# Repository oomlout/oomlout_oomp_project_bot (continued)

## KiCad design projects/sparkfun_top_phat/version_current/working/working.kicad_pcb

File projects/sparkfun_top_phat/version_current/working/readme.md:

# Top_pHat by sparkfun  
This is a harvested standardized copy of a project from github.  
The original project can be found at:  
https://github.com/sparkfun/Top_pHat  
Please consult that link for additional, details, files, and license information.  
Note: It was auto harvested and if the original repo had more than one board file or anything out of the ordinary the files here are likely not representative.

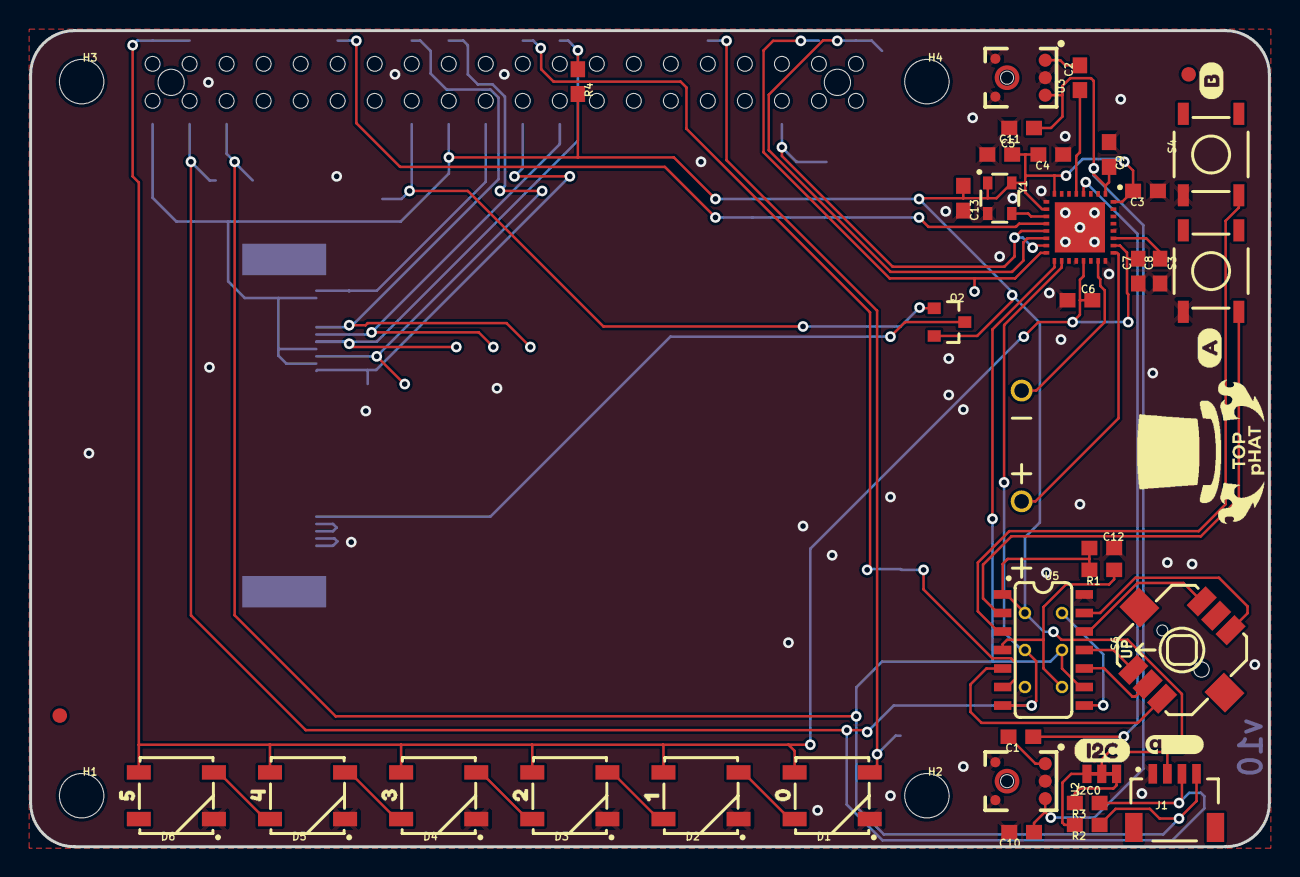
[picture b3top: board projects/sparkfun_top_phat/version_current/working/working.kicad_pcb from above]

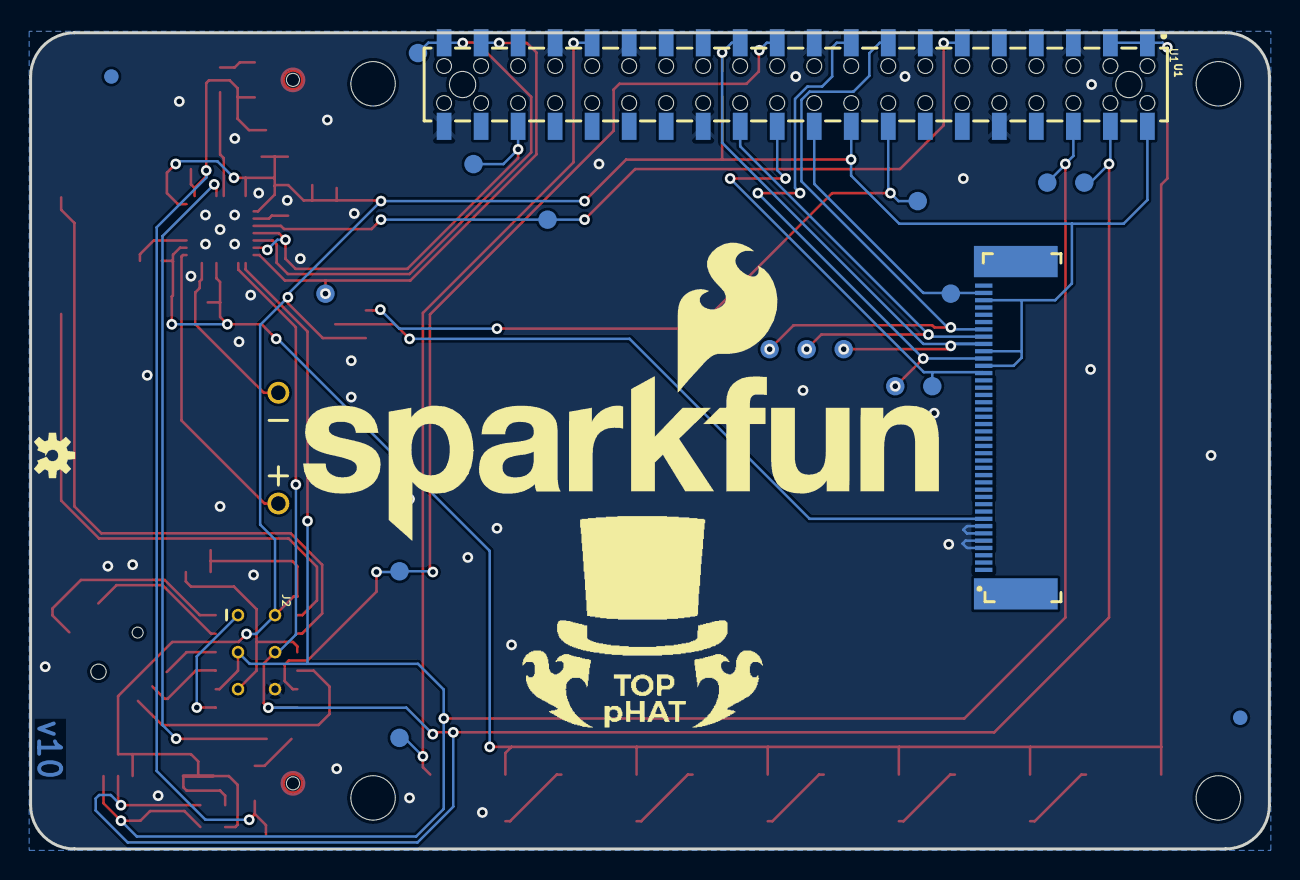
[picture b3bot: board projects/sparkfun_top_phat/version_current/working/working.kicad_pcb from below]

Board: 2 copper layers, 85.0 x 56.0 mm, 76 parts (23 on the bottom side), 44 nets.

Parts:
C1, C2: 2.2uF; 0603
C3, C4, C5, C10, C11, C12: 0.1uF; 0603
C6, C7, C8, C9: 4.7uF; 0603
C13: 10nF; 0603
D1, D2, D3, D4, D5, D6: WS2812B
FD1, FD2, FD3, FD4: FIDUCIAL1X2; FIDUCIAL-1X2
FRAME1: FRAME-LEDGER; CREATIVE_COMMONS
H1, H2, H3, H4: STAND-OFFTIGHT; STAND-OFF-TIGHT
I2C0: JUMPER-SMT_3_2-NC_TRACE_NO-SILK; SMT-JUMPER_3_2-NC_TRACE_NO-SILK
J1: QWIIC; JST04_1MM_RA
J2: AVR_SPI_PROG_3X2TESTPOINTS; 2X3_TEST_POINTS
J3: 2.4" TFT; FPC05040-17204
LOGO2: SFE_LOGO_NAME_FLAME.4_INCH; SFE_LOGO_NAME_FLAME_.4
LOGO3: QWIIC_LOGO_4MM; QWIIC_4MM
LOGO4: OSHW-LOGOS; OSHW-LOGO-S
LS2: CVS-1508; CVS-1508_PCBSPKR
Q2: 1.1A/60V/600mΩ; SOT23-3
R1, R4: 10k; 0603
R2, R3: 4.7k; 0603
S3, S4: MOMENTARY-SWITCH-SPST-SMD-5.2MM-TALL; TACTILE_SWITCH_SMD_5.2MM
S6: Joystick; JOYSTICK_MINI
TP1, TP2, TP3, TP4, TP5, TP6, TP7, TP8, TP9, TP10, TP11, TP12, TP13, TP14, TP15: TEST-POINT3X5; PAD.03X.05
U1: Raspberry Pi Header; RASPBERRY_PI_SHIELD_BOTTOM_ENTRY_NOHOLES
U2, U3: ADMP401
U4: WM8960; QFN-32
U5: ATTINY84; SO14
U$1, U$12: 2020#02#27#PNG
U$3: 00
U$4: 11
U$5: 22
U$6: A0
U$7: B1
U$8: I2C3
U$9: 33
U$10: 44
U$11: 55
Y1: 24 MHz; RESONATOR-SMD-3.2X2.5

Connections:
3.3V: C3.2, C4.2, C5.2, C12.1, C13.1, I2C0.2, J1.2, J2.2, J3.29, J3.31, J3.38, Q2.2, R1.2, R4.2, U1.1, U1.17, U4.8, U4.10, U4.32, U5.1, Y1.1, Y1.4
5V: C6.2, C7.2, D1.1, D2.1, D3.1, D4.1, D5.1, D6.1, U1.2, U1.4, U4.21, U4.26
ADC-DAT: TP10.P$1, U1.38, U4.16
BCLK: TP8.P$1, U1.12, U4.12
BTN_A: S3.3, U5.2
BTN_B: S4.3, U5.3
BTN_CENTER: S6.CTR, U5.10
BTN_DOWN: S6.D, U5.13
BTN_LEFT: S6.C, U5.5
BTN_RIGHT: S6.B, U5.12
BTN_UP: S6.A, U5.11
D/C: J3.30, TP14.P$1, U1.18
DAC-DAT: TP11.P$1, U1.40, U4.14
DAC-LRC: TP9.P$1, U1.35, U4.13, U4.15
GND: C3.1, C4.1, C5.1, C6.1, C7.1, C8.1, C9.1, C10.2, C11.2, C12.2, C13.2, D1.3, D2.3, D3.3, D4.3, D5.3, D6.3, J1.1, J2.6, J3.1, J3.4, J3.5, J3.6, J3.7, J3.11, J3.12, J3.13, J3.14, J3.15, J3.16, J3.17, J3.18, J3.19, J3.20, J3.21, J3.22, J3.23, J3.24, J3.25, J3.26, J3.27, J3.40, S3.1, S4.1, S6.GND, U1.6, U1.9, U1.14, U1.20, U1.25, U1.30, U1.34, U1.39, U2.2, U2.4, U2.6, U3.2, U3.4, U3.6, U4.9, U4.20, U4.24, U4.28, U4.PADDLE, U5.14, Y1.2
LED_DATA: D1.4, TP7.P$1, U1.32
LEFTMIC: C1.2, U2.1
MICBIAS: C9.2, C10.1, C11.1, U2.5, U3.5, U4.1
MISO: J2.1, U5.8
unnamed: D3.2, D4.4
unnamed: D4.2, D5.4
unnamed: D5.2, D6.4
unnamed: J3.8, Q2.3
unnamed: LS2.+, U4.25
unnamed: D1.2, D2.4
unnamed: D2.2, D3.4
unnamed: U4.11, Y1.3
unnamed: I2C0.3, R2.2
unnamed: I2C0.1, R3.2
unnamed: LS2.-, U4.23
unnamed: C1.1, U4.4
unnamed: C2.1, U4.5
unnamed: C8.2, U4.27
RIGHTMIC: C2.2, U3.1
SCK: J3.33, TP5.P$1, U1.23
SCL: J1.4, J2.3, R2.1, TP1.P$1, U1.5, U4.17, U5.9
SDA: J1.3, J2.4, R3.1, TP2.P$1, U1.3, U4.18, U5.7
SDI: J3.39, TP3.P$1, U1.19
SDO: J3.28, TP4.P$1, U1.21
~BKLITE: Q2.1, TP12.P$1, U1.15
~CS: J3.32, R4.1, TP6.P$1, U1.24
~INT: TP15.P$1, U1.22, U5.6
~RST_ATTINY: J2.5, R1.1, U5.4
~RST_SCREEN: J3.34, TP13.P$1, U1.16

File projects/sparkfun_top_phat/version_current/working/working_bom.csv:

"Id";"Designator";"Footprint";"Quantity";"Designation";"Supplier and ref";
1;"U$6";"A0";1;"";;;
2;"D2,D3,D6,D4,D5,D1";"WS2812B";6;"WS2812B";;;
3;"C3,C10,C5,C11,C12,C4";"0603";6;"0.1uF";;;
4;"FD3,FD1,FD2,FD4";"FIDUCIAL-1X2";4;"FIDUCIAL1X2";;;
5;"I2C0";"SMT-JUMPER_3_2-NC_TRACE_NO-SILK";1;"JUMPER-SMT_3_2-NC_TRACE_NO-SILK";;;
6;"U$4";"11";1;"";;;
7;"U$10";"44";1;"";;;
8;"U5";"SO14";1;"ATTINY84";;;
9;"U$9";"33";1;"";;;
10;"R1,R4";"0603";2;"10k";;;
11;"Y1";"RESONATOR-SMD-3.2X2.5";1;"24 MHz";;;
12;"R3,R2";"0603";2;"4.7k";;;
13;"LOGO3";"QWIIC_4MM";1;"QWIIC_LOGO_4MM";;;
14;"C2,C1";"0603";2;"2.2uF";;;
15;"U2,U3";"ADMP401";2;"ADMP401";;;
16;"H4,H1,H2,H3";"STAND-OFF-TIGHT";4;"STAND-OFFTIGHT";;;
17;"C8,C9,C6,C7";"0603";4;"4.7uF";;;
18;"C13";"0603";1;"10nF";;;
19;"U$3";"00";1;"";;;
20;"U$5";"22";1;"";;;
21;"J1";"JST04_1MM_RA";1;"QWIIC";;;
22;"U4";"QFN-32";1;"WM8960";;;
23;"U$11";"55";1;"";;;
24;"U$1,U$12";"2020#02#27#PNG";2;"";;;
25;"S3,S4";"TACTILE_SWITCH_SMD_5.2MM";2;"MOMENTARY-SWITCH-SPST-SMD-5.2MM-TALL";;;
26;"U$7";"B1";1;"";;;
27;"U$8";"I2C3";1;"";;;
28;"S6";"JOYSTICK_MINI";1;"Joystick";;;
29;"LS2";"CVS-1508_PCBSPKR";1;"CVS-1508";;;
30;"Q2";"SOT23-3";1;"1.1A/60V/600mΩ";;;
31;"FRAME1";"CREATIVE_COMMONS";1;"FRAME-LEDGER";;;
32;"TP6,TP2,TP8,TP14,TP5,TP11,TP9,TP4,TP7,TP15,TP12,TP13,TP3,TP10,TP1";"PAD.03X.05";15;"TEST-POINT3X5";;;
33;"U1";"RASPBERRY_PI_SHIELD_BOTTOM_ENTRY_NOHOLES";1;"Raspberry Pi Header";;;
34;"LOGO4";"OSHW-LOGO-S";1;"OSHW-LOGOS";;;
35;"LOGO2";"SFE_LOGO_NAME_FLAME_.4";1;"SFE_LOGO_NAME_FLAME.4_INCH";;;
36;"J3";"FPC05040-17204";1;"2.4" TFT";;;
37;"J2";"2X3_TEST_POINTS";1;"AVR_SPI_PROG_3X2TESTPOINTS";;;

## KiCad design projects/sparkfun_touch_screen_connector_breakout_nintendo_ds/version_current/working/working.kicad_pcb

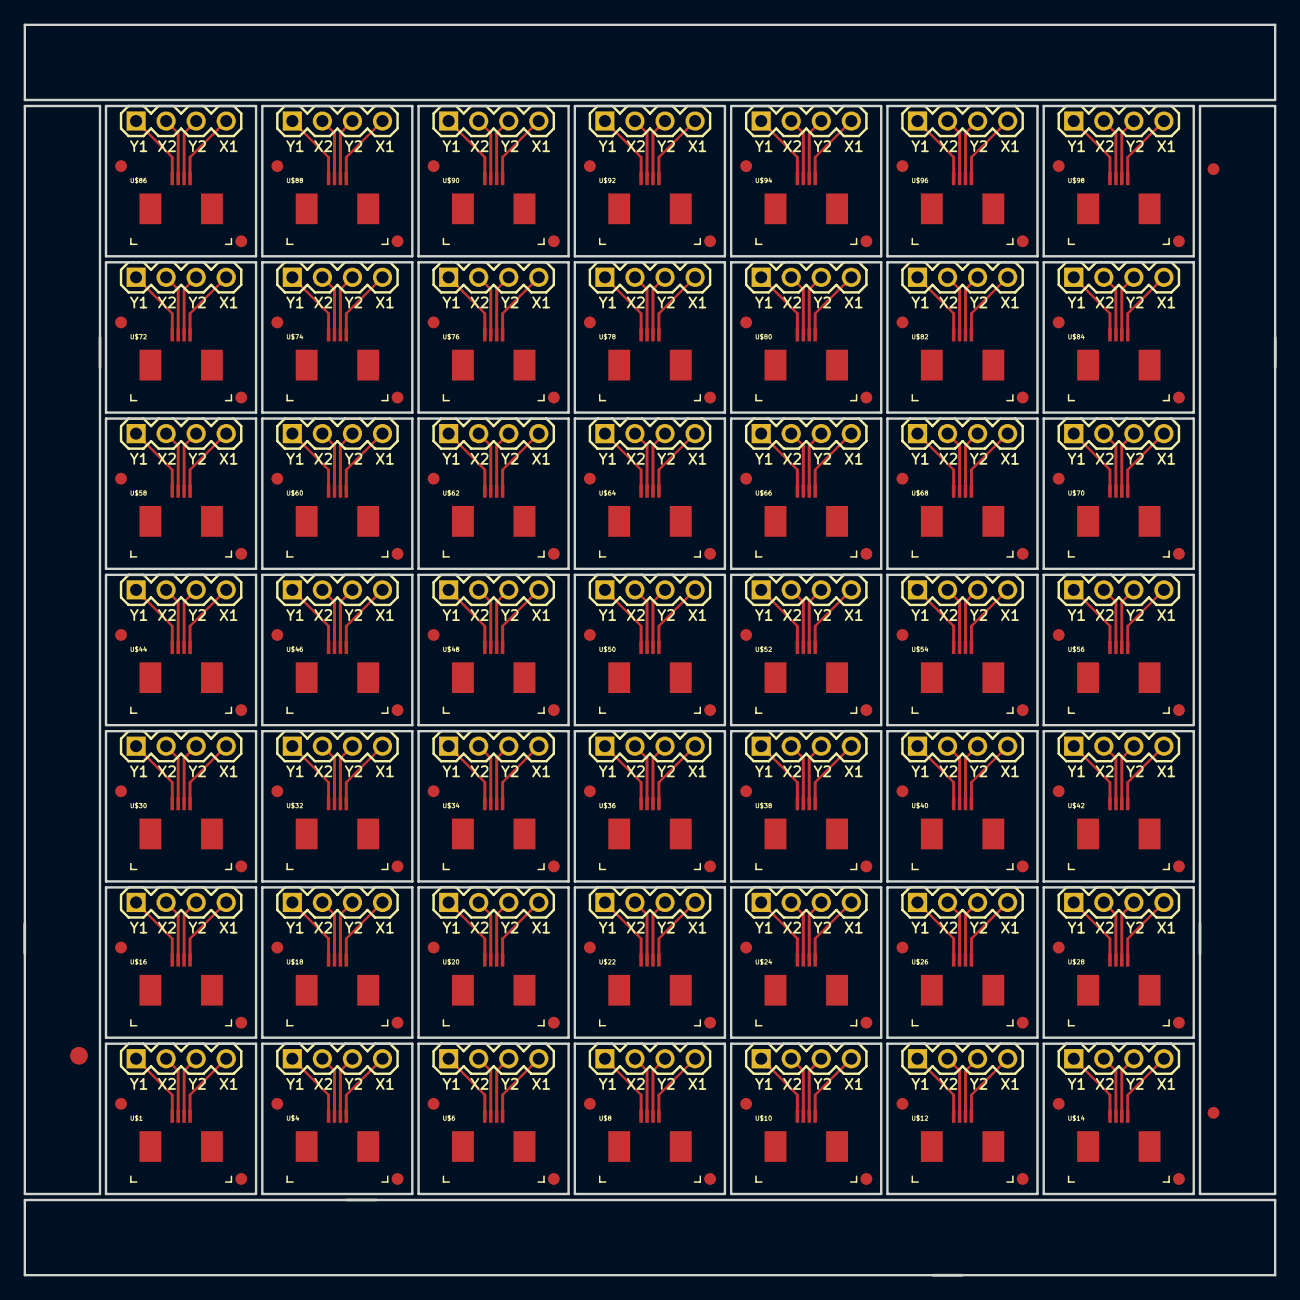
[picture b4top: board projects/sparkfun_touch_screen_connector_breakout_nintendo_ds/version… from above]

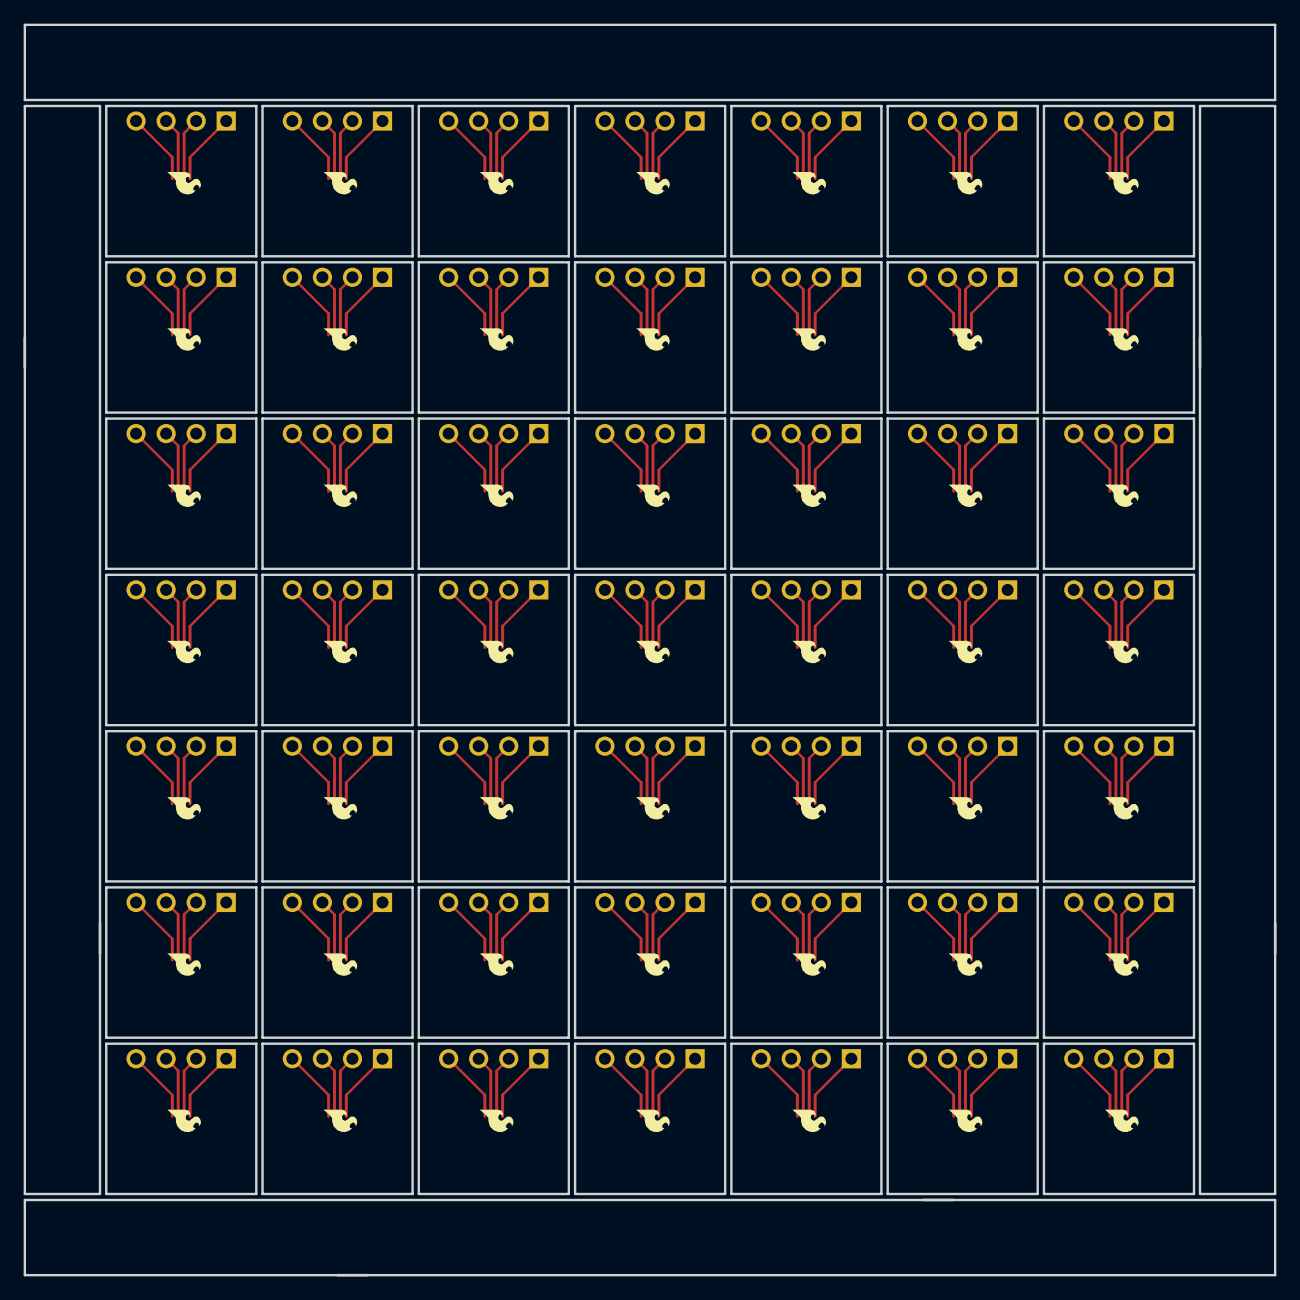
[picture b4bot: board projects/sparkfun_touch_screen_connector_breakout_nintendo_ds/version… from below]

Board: 16 copper layers, 105.7 x 105.7 mm, 248 parts (49 on the bottom side), 196 nets.

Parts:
E$1: FIDUCIAL-1.5X3
E$5, E$6: FIDUCIAL-1X2
FID1, FID2, FID3, FID4, FID5, FID6, FID7, FID8, FID9, FID10, FID11, FID12, FID13, FID14, FID15, FID16, FID17, FID18, FID19, FID20, FID21, FID22, FID23, FID24, FID25, FID26, FID27, FID28, FID29, FID30, FID31, FID32, FID33, FID34, FID35, FID36, FID37, FID38, FID39, FID40, FID41, FID42, FID43, FID44, FID45, FID46, FID47, FID48, FID49, FID50, FID51, FID52, FID53, FID54, FID55, FID56, FID57, FID58, FID59, FID60, FID61, FID62, FID63, FID64, FID65, FID66, FID67, FID68, FID69, FID70, FID71, FID72, FID73, FID74, FID75, FID76, FID77, FID78, FID79, FID80, FID81, FID82, FID83, FID84, FID85, FID86, FID87, FID88, FID89, FID90, FID91, FID92, FID93, FID94, FID95, FID96, FID97, FID98: FIDUCIAL1X2; FIDUCIAL-1X2
JP1, JP2, JP3, JP4, JP5, JP6, JP7, JP8, JP9, JP10, JP11, JP12, JP13, JP14, JP15, JP16, JP17, JP18, JP19, JP20, JP21, JP22, JP23, JP24, JP25, JP26, JP27, JP28, JP29, JP30, JP31, JP32, JP33, JP34, JP35, JP36, JP37, JP38, JP39, JP40, JP41, JP42, JP43, JP44, JP45, JP46, JP47, JP48, JP49: 1X04
U$1, U$4, U$6, U$8, U$10, U$12, U$14, U$16, U$18, U$20, U$22, U$24, U$26, U$28, U$30, U$32, U$34, U$36, U$38, U$40, U$42, U$44, U$46, U$48, U$50, U$52, U$54, U$56, U$58, U$60, U$62, U$64, U$66, U$68, U$70, U$72, U$74, U$76, U$78, U$80, U$82, U$84, U$86, U$88, U$90, U$92, U$94, U$96, U$98: DS_TOUCH_CONNECTOR
U$2, U$3, U$5, U$7, U$9, U$11, U$13, U$15, U$17, U$19, U$21, U$23, U$25, U$27, U$29, U$31, U$33, U$35, U$37, U$39, U$41, U$43, U$45, U$47, U$49, U$51, U$53, U$55, U$57, U$59, U$61, U$63, U$65, U$67, U$69, U$71, U$73, U$75, U$77, U$79, U$81, U$83, U$85, U$87, U$89, U$91, U$93, U$95, U$97: LOGO-SFESK; SFE-LOGO-FLAME

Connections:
unnamed: JP1.4, U$1.X1
unnamed: JP1.3, U$1.Y2
unnamed: JP1.2, U$1.X2
unnamed: JP1.1, U$1.Y1
unnamed: JP2.4, U$4.X1
unnamed: JP2.3, U$4.Y2
unnamed: JP2.2, U$4.X2
unnamed: JP2.1, U$4.Y1
unnamed: JP3.4, U$6.X1
unnamed: JP3.3, U$6.Y2
unnamed: JP3.2, U$6.X2
unnamed: JP3.1, U$6.Y1
unnamed: JP4.4, U$8.X1
unnamed: JP4.3, U$8.Y2
unnamed: JP4.2, U$8.X2
unnamed: JP4.1, U$8.Y1
unnamed: JP5.4, U$10.X1
unnamed: JP5.3, U$10.Y2
unnamed: JP5.2, U$10.X2
unnamed: JP5.1, U$10.Y1
unnamed: JP6.4, U$12.X1
unnamed: JP6.3, U$12.Y2
unnamed: JP6.2, U$12.X2
unnamed: JP6.1, U$12.Y1
unnamed: JP7.4, U$14.X1
unnamed: JP7.3, U$14.Y2
unnamed: JP7.2, U$14.X2
unnamed: JP7.1, U$14.Y1
unnamed: JP8.4, U$16.X1
unnamed: JP8.3, U$16.Y2
unnamed: JP8.2, U$16.X2
unnamed: JP8.1, U$16.Y1
unnamed: JP9.4, U$18.X1
unnamed: JP9.3, U$18.Y2
unnamed: JP9.2, U$18.X2
unnamed: JP9.1, U$18.Y1
unnamed: JP10.4, U$20.X1
unnamed: JP10.3, U$20.Y2
unnamed: JP10.2, U$20.X2
unnamed: JP10.1, U$20.Y1
unnamed: JP11.4, U$22.X1
unnamed: JP11.3, U$22.Y2
unnamed: JP11.2, U$22.X2
unnamed: JP11.1, U$22.Y1
unnamed: JP12.4, U$24.X1
unnamed: JP12.3, U$24.Y2
unnamed: JP12.2, U$24.X2
unnamed: JP12.1, U$24.Y1
unnamed: JP13.4, U$26.X1
unnamed: JP13.3, U$26.Y2
unnamed: JP13.2, U$26.X2
unnamed: JP13.1, U$26.Y1
unnamed: JP14.4, U$28.X1
unnamed: JP14.3, U$28.Y2
unnamed: JP14.2, U$28.X2
unnamed: JP14.1, U$28.Y1
unnamed: JP15.4, U$30.X1
unnamed: JP15.3, U$30.Y2
unnamed: JP15.2, U$30.X2
unnamed: JP15.1, U$30.Y1
unnamed: JP16.4, U$32.X1
unnamed: JP16.3, U$32.Y2
unnamed: JP16.2, U$32.X2
unnamed: JP16.1, U$32.Y1
unnamed: JP17.4, U$34.X1
unnamed: JP17.3, U$34.Y2
unnamed: JP17.2, U$34.X2
unnamed: JP17.1, U$34.Y1
unnamed: JP18.4, U$36.X1
unnamed: JP18.3, U$36.Y2
unnamed: JP18.2, U$36.X2
unnamed: JP18.1, U$36.Y1
unnamed: JP19.4, U$38.X1
unnamed: JP19.3, U$38.Y2
unnamed: JP19.2, U$38.X2
unnamed: JP19.1, U$38.Y1
unnamed: JP20.4, U$40.X1
unnamed: JP20.3, U$40.Y2
unnamed: JP20.2, U$40.X2
unnamed: JP20.1, U$40.Y1
unnamed: JP21.4, U$42.X1
unnamed: JP21.3, U$42.Y2
unnamed: JP21.2, U$42.X2
unnamed: JP21.1, U$42.Y1
unnamed: JP22.4, U$44.X1
unnamed: JP22.3, U$44.Y2
unnamed: JP22.2, U$44.X2
unnamed: JP22.1, U$44.Y1
unnamed: JP23.4, U$46.X1
unnamed: JP23.3, U$46.Y2
unnamed: JP23.2, U$46.X2
unnamed: JP23.1, U$46.Y1
unnamed: JP24.4, U$48.X1
unnamed: JP24.3, U$48.Y2
unnamed: JP24.2, U$48.X2
unnamed: JP24.1, U$48.Y1
unnamed: JP25.4, U$50.X1
unnamed: JP25.3, U$50.Y2
unnamed: JP25.2, U$50.X2
unnamed: JP25.1, U$50.Y1
unnamed: JP26.4, U$52.X1
unnamed: JP26.3, U$52.Y2
unnamed: JP26.2, U$52.X2
unnamed: JP26.1, U$52.Y1
unnamed: JP27.4, U$54.X1
unnamed: JP27.3, U$54.Y2
unnamed: JP27.2, U$54.X2
unnamed: JP27.1, U$54.Y1
unnamed: JP28.4, U$56.X1
unnamed: JP28.3, U$56.Y2
unnamed: JP28.2, U$56.X2
unnamed: JP28.1, U$56.Y1
unnamed: JP29.4, U$58.X1
unnamed: JP29.3, U$58.Y2
unnamed: JP29.2, U$58.X2
unnamed: JP29.1, U$58.Y1
unnamed: JP30.4, U$60.X1
unnamed: JP30.3, U$60.Y2
unnamed: JP30.2, U$60.X2
unnamed: JP30.1, U$60.Y1
unnamed: JP31.4, U$62.X1
unnamed: JP31.3, U$62.Y2
unnamed: JP31.2, U$62.X2
unnamed: JP31.1, U$62.Y1
unnamed: JP32.4, U$64.X1
unnamed: JP32.3, U$64.Y2
unnamed: JP32.2, U$64.X2
unnamed: JP32.1, U$64.Y1
unnamed: JP33.4, U$66.X1
unnamed: JP33.3, U$66.Y2
unnamed: JP33.2, U$66.X2
unnamed: JP33.1, U$66.Y1
unnamed: JP34.4, U$68.X1
unnamed: JP34.3, U$68.Y2
unnamed: JP34.2, U$68.X2
unnamed: JP34.1, U$68.Y1
unnamed: JP35.4, U$70.X1
unnamed: JP35.3, U$70.Y2
unnamed: JP35.2, U$70.X2
unnamed: JP35.1, U$70.Y1
unnamed: JP36.4, U$72.X1
unnamed: JP36.3, U$72.Y2
unnamed: JP36.2, U$72.X2
unnamed: JP36.1, U$72.Y1
unnamed: JP37.4, U$74.X1
unnamed: JP37.3, U$74.Y2
unnamed: JP37.2, U$74.X2
unnamed: JP37.1, U$74.Y1
unnamed: JP38.4, U$76.X1
unnamed: JP38.3, U$76.Y2
unnamed: JP38.2, U$76.X2
unnamed: JP38.1, U$76.Y1
unnamed: JP39.4, U$78.X1
unnamed: JP39.3, U$78.Y2
unnamed: JP39.2, U$78.X2
unnamed: JP39.1, U$78.Y1
unnamed: JP40.4, U$80.X1
unnamed: JP40.3, U$80.Y2
unnamed: JP40.2, U$80.X2
unnamed: JP40.1, U$80.Y1
unnamed: JP41.4, U$82.X1
unnamed: JP41.3, U$82.Y2
unnamed: JP41.2, U$82.X2
unnamed: JP41.1, U$82.Y1
unnamed: JP42.4, U$84.X1
unnamed: JP42.3, U$84.Y2
unnamed: JP42.2, U$84.X2
unnamed: JP42.1, U$84.Y1
unnamed: JP43.4, U$86.X1
unnamed: JP43.3, U$86.Y2
unnamed: JP43.2, U$86.X2
unnamed: JP43.1, U$86.Y1
unnamed: JP44.4, U$88.X1
unnamed: JP44.3, U$88.Y2
unnamed: JP44.2, U$88.X2
unnamed: JP44.1, U$88.Y1
unnamed: JP45.4, U$90.X1
unnamed: JP45.3, U$90.Y2
unnamed: JP45.2, U$90.X2
unnamed: JP45.1, U$90.Y1
unnamed: JP46.4, U$92.X1
unnamed: JP46.3, U$92.Y2
unnamed: JP46.2, U$92.X2
unnamed: JP46.1, U$92.Y1
unnamed: JP47.4, U$94.X1
unnamed: JP47.3, U$94.Y2
unnamed: JP47.2, U$94.X2
unnamed: JP47.1, U$94.Y1
unnamed: JP48.4, U$96.X1
unnamed: JP48.3, U$96.Y2
unnamed: JP48.2, U$96.X2
unnamed: JP48.1, U$96.Y1
unnamed: JP49.4, U$98.X1
unnamed: JP49.3, U$98.Y2
unnamed: JP49.2, U$98.X2
unnamed: JP49.1, U$98.Y1

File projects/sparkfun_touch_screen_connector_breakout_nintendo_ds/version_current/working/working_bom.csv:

"Id";"Designator";"Footprint";"Quantity";"Designation";"Supplier and ref";
1;"U$10,U$62,U$60,U$64,U$14,U$78,U$34,U$86,U$72,U$32,U$74,U$16,U$76,U$70,U$38,U$6,U$4,U$26,U$90,U$94,U$44,U$40,U$88,U$24,U$48,U$82,U$20,U$28,U$80,U$42,U$68,U$54,U$56,U$84,U$22,U$1,U$46,U$52,U$92,U$58,U$96,U$36,U$12,U$98,U$8,U$50,U$66,U$30,U$18";"DS_TOUCH_CONNECTOR";49;"DS_TOUCH_CONNECTOR";;;
2;"FID72,FID11,FID44,FID38,FID70,FID96,FID33,FID17,FID20,FID23,FID48,FID86,FID19,FID49,FID15,FID8,FID90,FID34,FID52,FID27,FID61,FID79,FID62,FID84,FID83,FID64,FID26,FID73,FID69,FID98,FID46,FID12,FID45,FID94,FID60,FID78,FID59,FID89,FID5,FID51,FID35,FID2,FID81,FID76,FID6,FID43,FID16,FID56,FID31,FID95,FID66,FID88,FID10,FID58,FID53,FID71,FID87,FID14,FID41,FID85,FID91,FID13,FID77,FID22,FID7,FID18,FID28,FID9,FID40,FID4,FID80,FID63,FID67,FID24,FID42,FID65,FID82,FID30,FID54,FID57,FID39,FID1,FID32,FID93,FID21,FID97,FID47,FID55,FID37,FID50,FID3,FID74,FID25,FID29,FID75,FID92,FID68,FID36";"FIDUCIAL-1X2";98;"FIDUCIAL1X2";;;
3;"JP6,JP2,JP9,JP41,JP34,JP42,JP22,JP26,JP31,JP16,JP19,JP30,JP38,JP49,JP13,JP46,JP27,JP12,JP11,JP43,JP35,JP40,JP39,JP23,JP20,JP33,JP32,JP1,JP7,JP3,JP8,JP4,JP5,JP28,JP24,JP29,JP25,JP21,JP37,JP48,JP17,JP45,JP18,JP36,JP10,JP44,JP47,JP15,JP14";"1X04";49;"";;;
4;"E$1";"FIDUCIAL-1.5X3";1;"";;;
5;"E$6,E$5";"FIDUCIAL-1X2";2;"";;;
6;"U$63,U$77,U$41,U$79,U$9,U$91,U$69,U$29,U$37,U$43,U$83,U$89,U$93,U$31,U$27,U$3,U$21,U$87,U$5,U$7,U$47,U$45,U$73,U$13,U$2,U$11,U$49,U$35,U$97,U$61,U$75,U$23,U$33,U$57,U$71,U$65,U$25,U$39,U$15,U$53,U$55,U$59,U$95,U$51,U$17,U$85,U$19,U$81,U$67";"SFE-LOGO-FLAME";49;"LOGO-SFESK";;;

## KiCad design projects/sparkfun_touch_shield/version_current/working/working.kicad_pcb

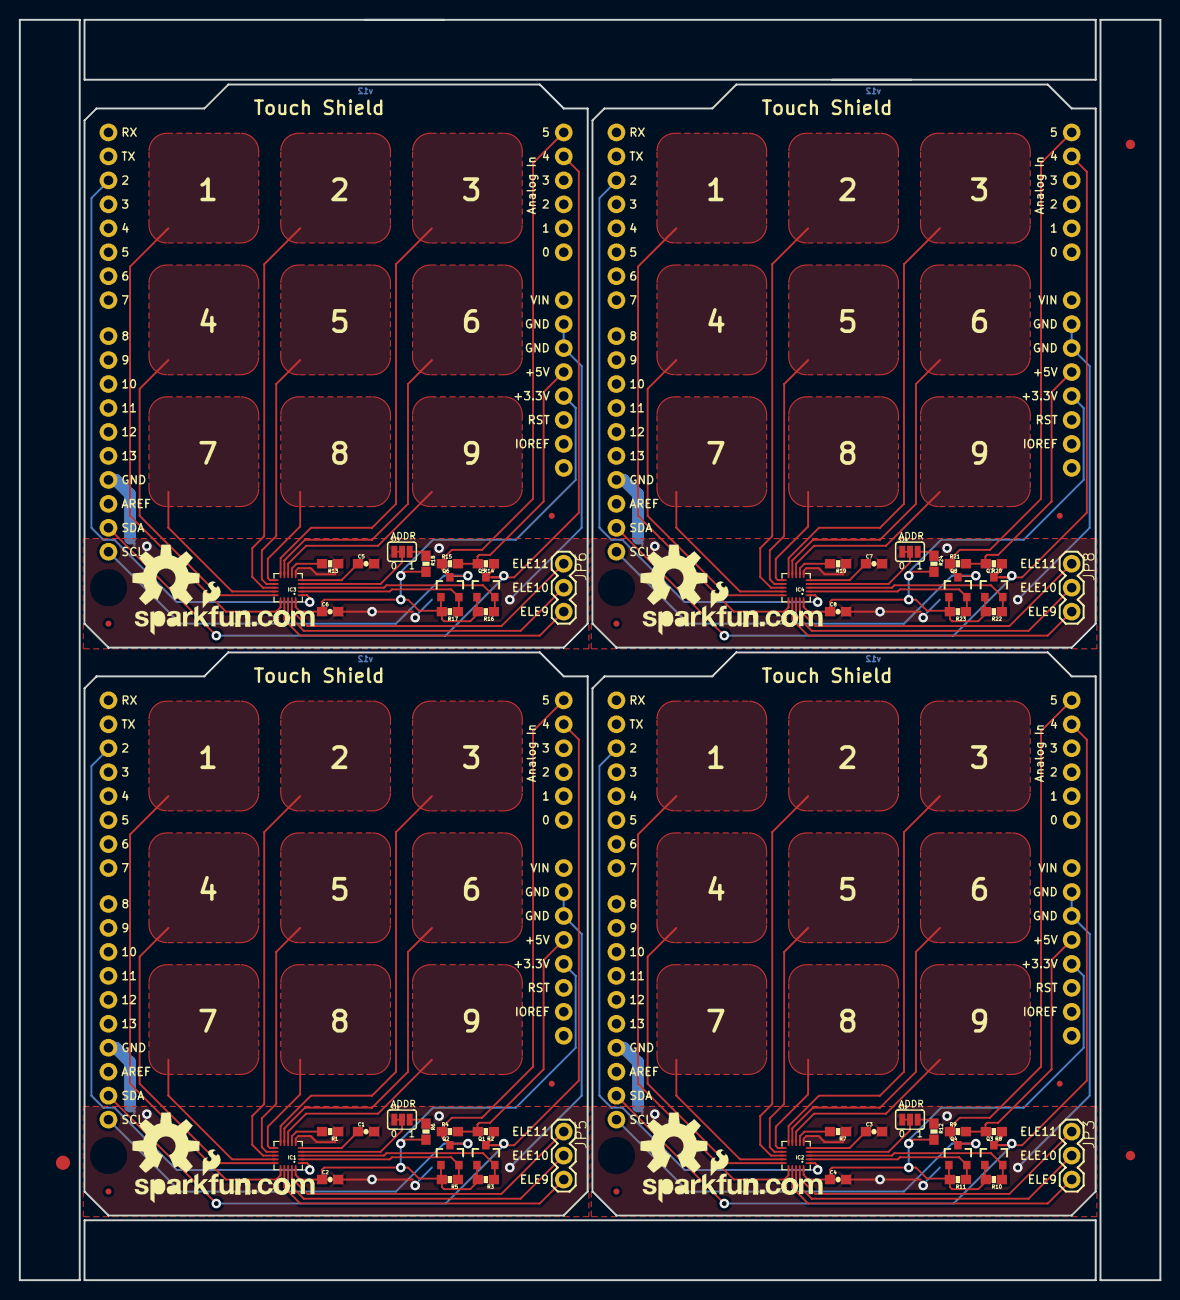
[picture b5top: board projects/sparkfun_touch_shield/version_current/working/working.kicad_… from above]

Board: 2 copper layers, 120.9 x 133.6 mm, 75 parts (0 on the bottom side), 60 nets.

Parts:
C1, C2, C3, C4, C5, C6, C7, C8: 0.1uF; 0603-CAP
E$1: FIDUCIAL-1.5X3
E$4, E$8: FIDUCIAL-1X2
FID1, FID2, FID3, FID4, FID5, FID6, FID7, FID8: FIDUCIALUFIDUCIAL; MICRO-FIDUCIAL
IC1, IC2, IC3, IC4: MPR121; QFN-20-0.4MM-V2
JP1, JP2, JP4, JP7: LOGO-SFENEW; SFE-NEW-WEBLOGO
JP3, JP5, JP6, JP8: extra; 1X03
Q1, Q2, Q3, Q4, Q5, Q6, Q7, Q8: BSS138; SOT23-3
R1, R7, R13, R19: 75k; 0603-RES
R2, R3, R4, R5, R8, R9, R10, R11, R14, R15, R16, R17, R20, R21, R22, R23: 10k; 0603-RES
R6, R12, R18, R24: 10K; 0603-RES
SJ1, SJ2, SJ3, SJ4: SJ_3_PASTE1&2
U1, U2, U3, U4: ARDUINO_R3_SHIELD; UNO_R3_SHIELD
U$1, U$2, U$3, U$5: OSHW-LOGOL; OSHW-LOGO-L

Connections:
3.3V: C2.1, IC1.20, Q1.1, Q2.1, R3.2, R5.2, R6.2, U1.3.3V
3.3V1: C4.1, IC2.20, Q3.1, Q4.1, R10.2, R11.2, R12.2, U2.3.3V
3.3V2: C6.1, IC3.20, Q5.1, Q6.1, R16.2, R17.2, R18.2, U3.3.3V
3.3V3: C8.1, IC4.20, Q7.1, Q8.1, R22.2, R23.2, R24.2, U4.3.3V
5V: R2.2, R4.2, U1.5V
5V1: R8.2, R9.2, U2.5V
5V2: R14.2, R15.2, U3.5V
5V3: R20.2, R21.2, U4.5V
*IRQ: IC1.1, U1.D2
*IRQ1: IC2.1, U2.D2
*IRQ2: IC3.1, U3.D2
*IRQ3: IC4.1, U4.D2
ELE1: IC2.19, JP3.1
ELE2: IC2.18, JP3.2
ELE3: IC2.17, JP3.3
ELE4: IC3.19, JP6.1
ELE5: IC3.18, JP6.2
ELE6: IC3.17, JP6.3
ELE7: IC4.19, JP8.1
ELE8: IC4.18, JP8.2
ELE9: IC1.17, JP5.3
ELE10: IC1.18, JP5.2
ELE11: IC1.19, JP5.1
ELE12: IC4.17, JP8.3
GND: C1.2, C2.2, IC1.6, R1.1, SJ1.1, U1.GND@0, U1.GND@1, U1.GND@2
GND1: C3.2, C4.2, IC2.6, R7.1, SJ2.1, U2.GND@0, U2.GND@1, U2.GND@2
GND2: C5.2, C6.2, IC3.6, R13.1, SJ3.1, U3.GND@0, U3.GND@1, U3.GND@2
GND3: C7.2, C8.2, IC4.6, R19.1, SJ4.1, U4.GND@0, U4.GND@1, U4.GND@2
unnamed: IC1.4, SJ1.2
unnamed: R6.1, SJ1.3
unnamed: IC2.4, SJ2.2
unnamed: R12.1, SJ2.3
unnamed: IC3.4, SJ3.2
unnamed: R18.1, SJ3.3
unnamed: IC4.4, SJ4.2
unnamed: R24.1, SJ4.3
REXT: IC1.7, R1.2
REXT1: IC2.7, R7.2
REXT2: IC3.7, R13.2
REXT3: IC4.7, R19.2
SCL_H: Q2.3, R4.1, U1.A5, U1.SCL
SCL_H1: Q4.3, R9.1, U2.A5, U2.SCL
SCL_H2: Q6.3, R15.1, U3.A5, U3.SCL
SCL_H3: Q8.3, R21.1, U4.A5, U4.SCL
SCL_L: IC1.2, Q2.2, R5.1
SCL_L1: IC2.2, Q4.2, R11.1
SCL_L2: IC3.2, Q6.2, R17.1
SCL_L3: IC4.2, Q8.2, R23.1
SDA_H: Q1.3, R2.1, U1.A4, U1.SDA
SDA_H1: Q3.3, R8.1, U2.A4, U2.SDA
SDA_H2: Q5.3, R14.1, U3.A4, U3.SDA
SDA_H3: Q7.3, R20.1, U4.A4, U4.SDA
SDA_L: IC1.3, Q1.2, R3.1
SDA_L1: IC2.3, Q3.2, R10.1
SDA_L2: IC3.3, Q5.2, R16.1
SDA_L3: IC4.3, Q7.2, R22.1
VREG: C1.1, IC1.5
VREG1: C3.1, IC2.5
VREG2: C5.1, IC3.5
VREG3: C7.1, IC4.5

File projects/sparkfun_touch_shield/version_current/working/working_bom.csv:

"Id";"Designator";"Footprint";"Quantity";"Designation";"Supplier and ref";
1;"Q1,Q6,Q3,Q5,Q7,Q2,Q4,Q8";"SOT23-3";8;"BSS138";;;
2;"U$2,U$1,U$3,U$5";"OSHW-LOGO-L";4;"OSHW-LOGOL";;;
3;"R3,R11,R14,R23,R17,R10,R22,R16,R2,R8,R9,R15,R21,R4,R20,R5";"0603-RES";16;"10k";;;
4;"JP2,JP1,JP4,JP7";"SFE-NEW-WEBLOGO";4;"LOGO-SFENEW";;;
5;"FID4,FID2,FID3,FID1,FID8,FID7,FID5,FID6";"MICRO-FIDUCIAL";8;"FIDUCIALUFIDUCIAL";;;
6;"R24,R6,R18,R12";"0603-RES";4;"10K";;;
7;"U2,U4,U3,U1";"UNO_R3_SHIELD";4;"ARDUINO_R3_SHIELD";;;
8;"SJ3,SJ1,SJ2,SJ4";"SJ_3_PASTE1&2";4;"";;;
9;"IC1,IC4,IC3,IC2";"QFN-20-0.4MM-V2";4;"MPR121";;;
10;"R1,R13,R7,R19";"0603-RES";4;"75k";;;
11;"C1,C3,C4,C8,C7,C2,C6,C5";"0603-CAP";8;"0.1uF";;;
12;"JP8,JP5,JP6,JP3";"1X03";4;"extra";;;
13;"E$4,E$8";"FIDUCIAL-1X2";2;"";;;
14;"E$1";"FIDUCIAL-1.5X3";1;"";;;

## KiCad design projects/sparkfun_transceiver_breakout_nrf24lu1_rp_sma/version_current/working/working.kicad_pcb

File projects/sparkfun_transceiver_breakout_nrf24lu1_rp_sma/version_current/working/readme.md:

# Transceiver_Breakout-nRF24LU1_RP-SMA by sparkfun  
This is a harvested standardized copy of a project from github.  
The original project can be found at:  
https://github.com/sparkfun/Transceiver_Breakout-nRF24LU1_RP-SMA  
Please consult that link for additional, details, files, and license information.  
Note: It was auto harvested and if the original repo had more than one board file or anything out of the ordinary the files here are likely not representative.

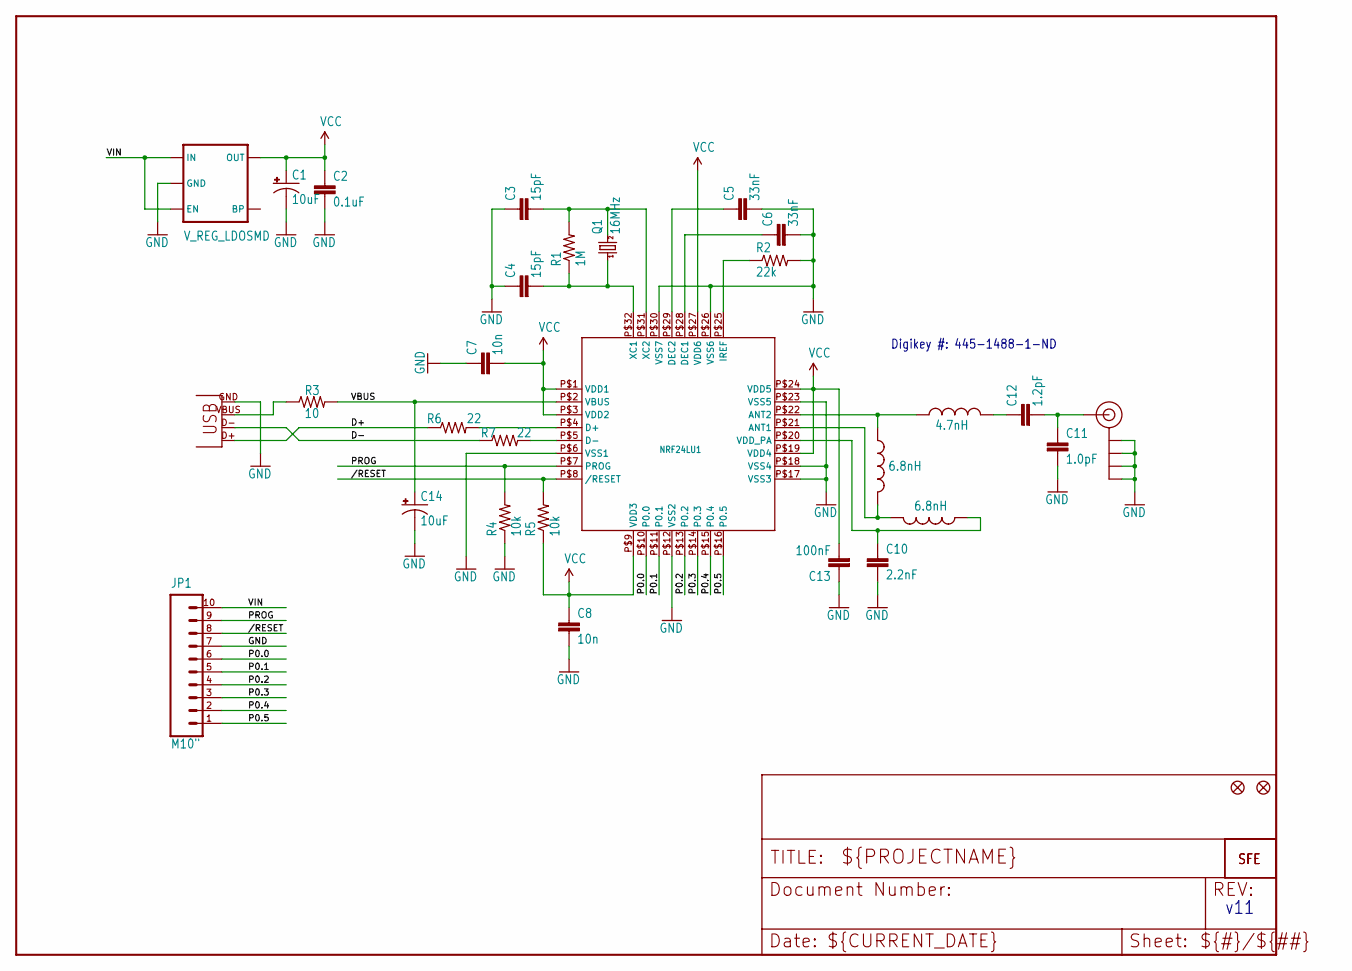
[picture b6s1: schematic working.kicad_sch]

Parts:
C1, C14: 10uF; EIA3216
C2: 0.1uF; 0402-CAP
C3, C4: 15pF; 0402-CAP
C5, C6: 33nF; 0402-CAP
C7, C8: 10n; 0402-CAP
C10: 2.2nF; 0402-CAP
C11: 1.0pF; 0402-CAP
C12: 1.2pF; 0402-CAP
C13: 100nF; 0402-CAP
J$1: SMA_EDGE; SMA-EDGE
JP1: M10"; 1X10
JP2: LOGO-SFENEW; SFE-NEW-WEBLOGO
L1: 4.7nH; C0402
L2, L3: 6.8nH; C0402
Q1: 16MHz; CRYSTAL-SMD-5X3
R1: 1M; 0402-RES
R2: 22k; 0402-RES
R3: 10; 1206
R4, R5: 10k; 0402-RES
R6, R7: 22; 0402-RES
U1: V_REG_LDOSMD; SOT23-5
U2: NRF24LU1; QFN-32
U$12, U$13: FIDUCIAL1X2; FIDUCIAL-1X2
U$14: LOGO-SFESK; SFE-LOGO-FLAME
X1: USBSMD; USB-MINIB

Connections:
/RESET: JP1.8, R5.2, U2.P$8 (/RESET)
D+: R6.1, X1.D+
D-: R7.1, X1.D-
GND: C1.C (-), C2.2, C3.1, C4.1, C5.2, C6.2, C7.1, C8.2, C10.2, C11.2, C13.1, C14.C (-), J$1.GND@0, J$1.GND@1, J$1.GND@2, J$1.GND@3, JP1.7, R2.2, R4.1, U1.2 (GND), U2.P$6 (VSS1), U2.P$12 (VSS2), U2.P$17 (VSS3), U2.P$18 (VSS4), U2.P$23 (VSS5), U2.P$26 (VSS6), U2.P$30 (VSS7), X1.GND
unnamed: C3.2, Q1.3 (2), R1.2, U2.P$31 (XC2)
unnamed: C4.2, Q1.1, R1.1, U2.P$32 (XC1)
unnamed: L1.1, L2.1, U2.P$22 (ANT2)
unnamed: C5.1, U2.P$29 (DEC2)
unnamed: R6.2, U2.P$4 (D+)
unnamed: R3.1, X1.VBUS
unnamed: R7.2, U2.P$5 (D-)
unnamed: C6.1, U2.P$28 (DEC1)
unnamed: R2.1, U2.P$25 (IREF)
unnamed: C12.1, L1.2
unnamed: C11.1, C12.2, J$1.SIG (SIGNAL)
unnamed: L2.2, L3.2, U2.P$21 (ANT1)
unnamed: C10.1, L3.1, U2.P$20 (VDD_PA)
P0.0: JP1.6, U2.P$10 (P0.0)
P0.1: JP1.5, U2.P$11 (P0.1)
P0.2: JP1.4, U2.P$13 (P0.2)
P0.3: JP1.3, U2.P$14 (P0.3)
P0.4: JP1.2, U2.P$15 (P0.4)
P0.5: JP1.1, U2.P$16 (P0.5)
PROG: JP1.9, R4.2, U2.P$7 (PROG)
VBUS: C14.A (+), R3.2, U2.P$2 (VBUS)
VCC: C1.A (+), C2.1, C7.2, C8.1, C13.2, R5.1, U1.5 (OUT), U2.P$1 (VDD1), U2.P$3 (VDD2), U2.P$9 (VDD3), U2.P$19 (VDD4), U2.P$24 (VDD5), U2.P$27 (VDD6)
VIN: JP1.10, U1.1 (IN), U1.3 (EN)

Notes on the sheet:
v11
Digikey #: 445-1488-1-ND

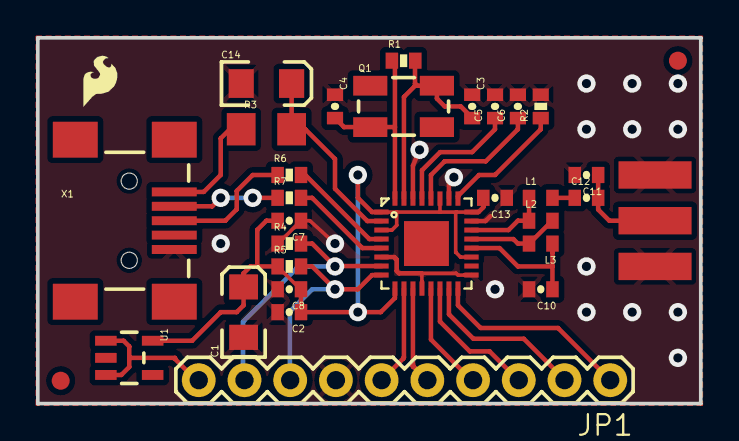
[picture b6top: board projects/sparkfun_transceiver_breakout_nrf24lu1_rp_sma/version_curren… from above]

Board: 2 copper layers, 36.8 x 20.3 mm, 33 parts (1 on the bottom side), 27 nets.

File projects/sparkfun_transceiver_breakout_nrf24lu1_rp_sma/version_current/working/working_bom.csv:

"Id";"Designator";"Footprint";"Quantity";"Designation";"Supplier and ref";
1;"U2";"QFN-32";1;"NRF24LU1";;;
2;"R5,R4";"0402-RES";2;"10k";;;
3;"Q1";"CRYSTAL-SMD-5X3";1;"16MHz";;;
4;"R6,R7";"0402-RES";2;"22";;;
5;"L2,L3";"C0402";2;"6.8nH";;;
6;"J$1";"SMA-EDGE";1;"SMA_EDGE";;;
7;"R1";"0402-RES";1;"1M";;;
8;"C3,C4";"0402-CAP";2;"15pF";;;
9;"C6,C5";"0402-CAP";2;"33nF";;;
10;"R3";"1206";1;"10";;;
11;"C7,C8";"0402-CAP";2;"10n";;;
12;"C14,C1";"EIA3216";2;"10uF";;;
13;"U$13,U$12";"FIDUCIAL-1X2";2;"FIDUCIAL1X2";;;
14;"C11";"0402-CAP";1;"1.0pF";;;
15;"U1";"SOT23-5";1;"3.3V";;;
16;"C10";"0402-CAP";1;"2.2nF";;;
17;"R2";"0402-RES";1;"22k";;;
18;"C2";"0402-CAP";1;"0.1uF";;;
19;"U$14";"SFE-LOGO-FLAME";1;"LOGO-SFESK";;;
20;"L1";"C0402";1;"4.7nH";;;
21;"C12";"0402-CAP";1;"1.2pF";;;
22;"X1";"USB-MINIB";1;"USBSMD";;;
23;"JP1";"1X10";1;"M10"";;;
24;"C13";"0402-CAP";1;"100nF";;;
25;"JP2";"SFE-NEW-WEBLOGO";1;"LOGO-SFENEW";;;
